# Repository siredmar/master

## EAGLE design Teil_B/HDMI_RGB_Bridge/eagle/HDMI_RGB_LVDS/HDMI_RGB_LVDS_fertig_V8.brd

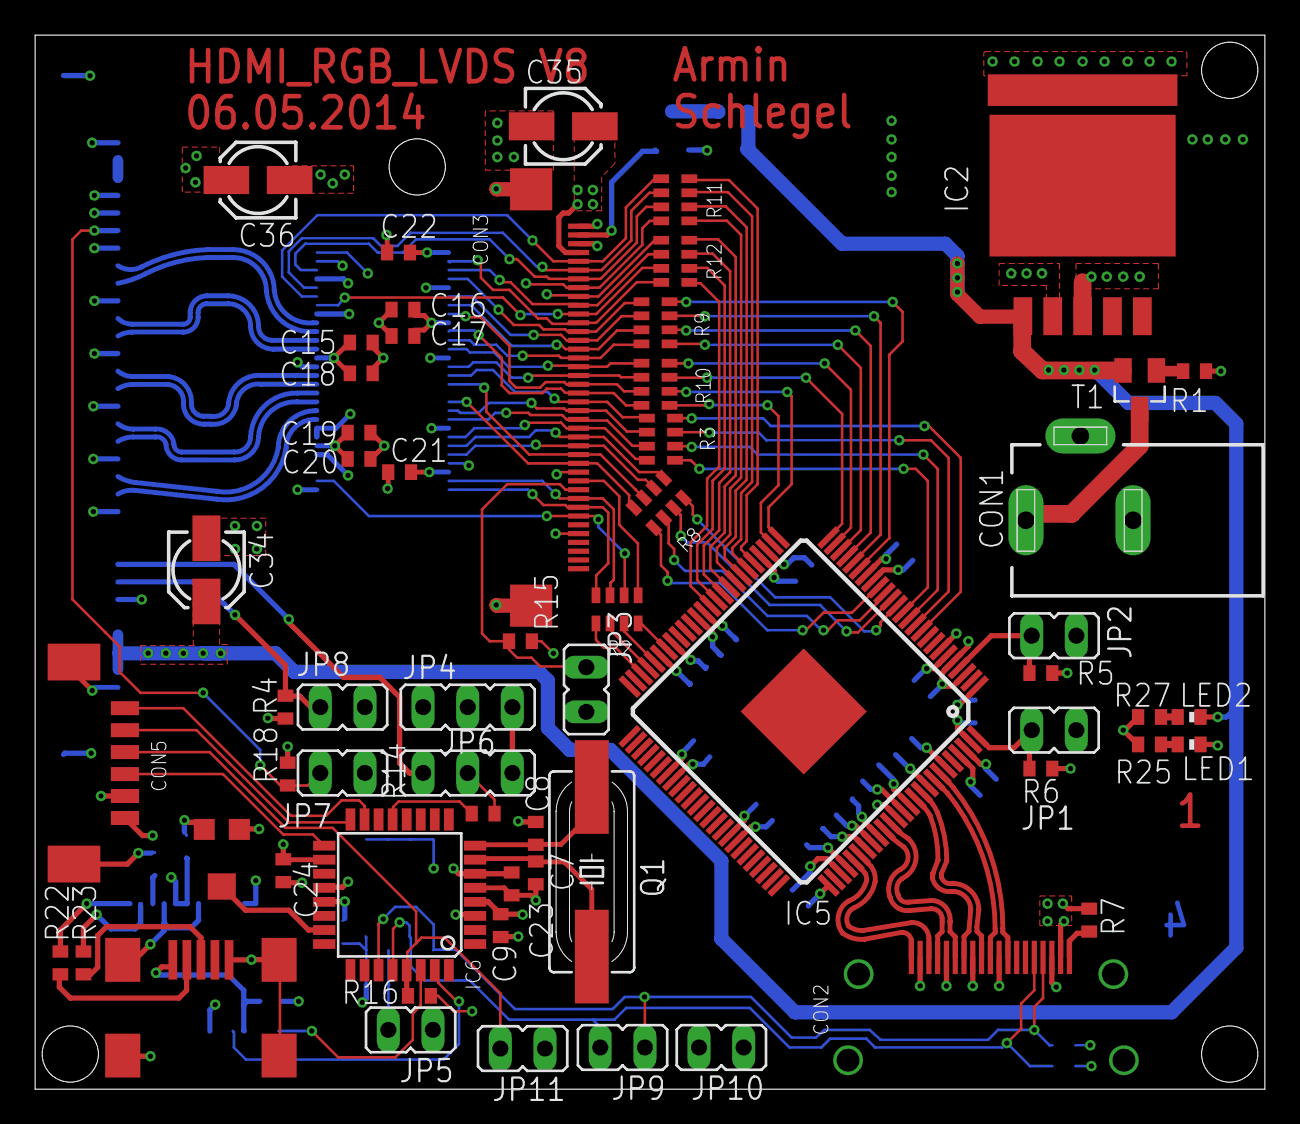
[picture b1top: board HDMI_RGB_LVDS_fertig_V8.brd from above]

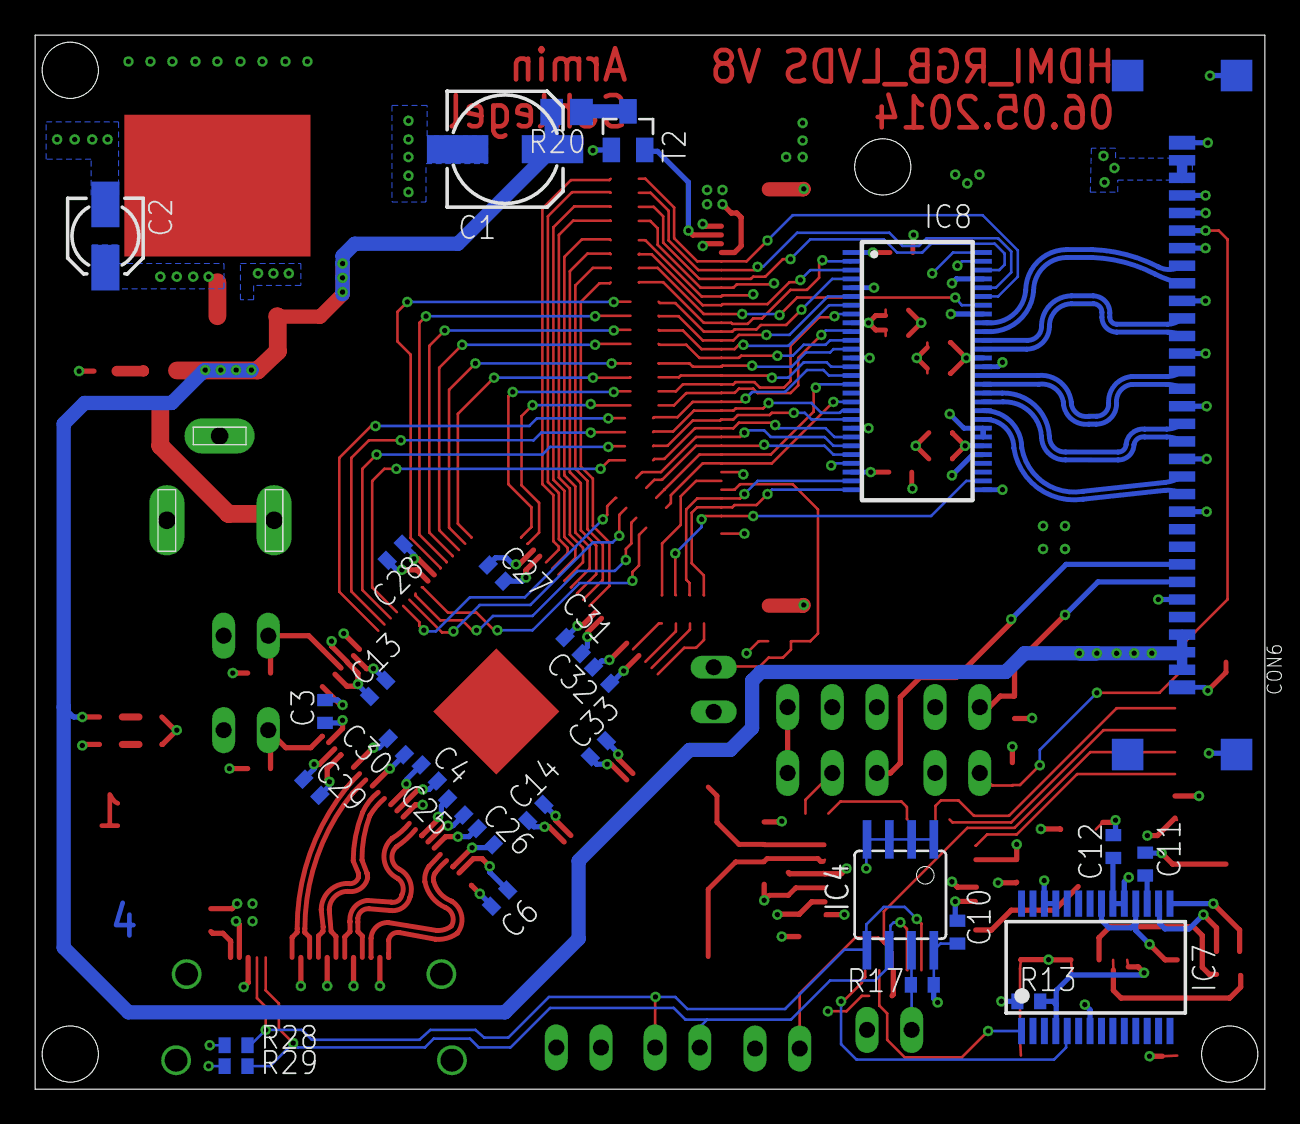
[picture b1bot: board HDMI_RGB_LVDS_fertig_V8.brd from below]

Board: 4 copper layers, 70.0 x 60.0 mm, 95 parts (29 on the bottom side), 113 nets.

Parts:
C1: 100u; C_POL_6X6MM
C2, C34, C35, C36: 10u; C_POL_4X4MM
C3, C4, C6, C9, C10, C11, C12, C13, C14, C16, C18, C20, C23, C24, C25, C26, C27, C28, C29, C30, C31, C32, C33: 100n; C0402
C7, C8: 22p; C0402
C15, C17, C19, C21, C22: 0.01u; C0402
CON1: KLDX-0202-A-LT
CON2: FCI-10029449-111RLF
CON3: XF2M-4015-1A
CON4: FCI-10033526-N3212LF
CON5: MOLEX-53261-0671
CON6: FI-X30SSLA-HF
IC2: WPMDL1300331BD; TO263-5
IC4: AT24C01C-SSHM-B; SOIC8
IC5: TFP401APZP; HTQFP-100
IC6: ATMEGA88PA; TQFP32
IC7: FT232RL; SSOP28
IC8: SN75LVDS83BDGGR; TSSOP-56
JP1, JP2, JP3, JP9, JP10: JUMPER2; JUMPER2_THROUGHHOLE
JP4, JP6: JUMPER3; JUMPER3_THROUGHHOLE
JP5, JP7, JP8, JP11: JUMPER2_THROUGHHOLE
LED1, LED2: LED0402
Q1: ATS073ASM-1; HC49/USSM
R1: 100k; R0402
R2, R3, R8, R9, R10, R11, R12: 22R; R-ARRAY-4X0603
R4, R5, R6, R7, R13, R15, R16, R17, R18: 10k; R0402
R14: 22R; R0402
R19: 5k; 35WR5KLFTR
R20: 15R; R2512
R22, R23: 0R; R0402
R25: 600R; R0402
R27: 2k5; R0402
R28, R29: 4k7; R0402
T1: IRLML5203TRPBF; SOT23
T2: IRLML2502TRPBF; SOT23
U$1, U$2, U$3, U$4, U$5, U$15: FRAME_A3_LANDSCAPE; FRAME

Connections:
+3V3: C2.+, C3.2, C4.2, C6.2, C13.2, C14.2, C15.2, C16.2, C17.2, C18.2, C19.2, C20.2, C21.2, C22.2, C25.2, C26.2, C27.2, C28.2, C29.2, C30.2, C31.2, C32.2, C33.2, C35.+, C36.+, CON3.4, CON6.29, CON6.30, IC2.3, IC5.6, IC5.18, IC5.29, IC5.38, IC5.43, IC5.57, IC5.67, IC5.78, IC5.82, IC5.84, IC5.88, IC5.95, IC5.97, IC5.99, IC8.1, IC8.9, IC8.26, IC8.34, IC8.44, JP4.1, LED1.C, R4.2, R5.2, R6.2, R15.2, R18.2
+5V: C9.1, C10.2, C23.1, C24.1, CON2.18, CON5.5, IC4.8, IC6.4, IC6.6, IC6.18, IC6.20, JP10.2, R7.2, R13.1, R16.1, R17.2, R19.1, R28.2, R29.2
+5V_USB: C12.1, CON4.1, IC7.4, IC7.19, IC7.20, R13.2
+12V: C1.+, C34.+, CON6.1, CON6.2, CON6.3, IC2.1, LED2.C, R20.2, T1.2
AVR_!RESET: CON5.3, IC6.29, JP11.2, R16.2
AVR_MISO: CON5.2, IC6.16
AVR_MOSI: CON5.1, IC6.15
AVR_PWM: JP6.2, R14.2
AVR_PWM_ADC: IC6.23, R19.2
AVR_SCK: CON5.4, IC6.17
AVR_XTAL1: C7.2, IC6.7, Q1.2
AVR_XTAL2: C8.2, IC6.8, Q1.1
EDID_SCL: CON2.15, IC4.6, IC6.28, JP9.2, R29.1
EDID_SDA: CON2.16, IC4.5, IC6.27, JP9.1, R28.1
EDID_WP: IC4.7, JP5.2, R17.1
FTDI_3V3OUT: C11.1, IC7.17
FTDI_RXD: IC6.31, IC7.5
FTDI_TXD: IC6.30, IC7.1
GND: C1.-, C2.-, C3.1, C4.1, C6.1, C7.1, C8.1, C9.2, C10.1, C11.2, C12.2, C13.1, C14.1, C15.1, C16.1, C17.1, C18.1, C19.1, C20.1, C21.1, C22.1, C23.2, C24.2, C25.1, C26.1, C27.1, C28.1, C29.1, C30.1, C31.1, C32.1, C33.1, C34.-, C35.-, C36.-, CON1.2, CON1.3, CON2.2, CON2.5, CON2.8, CON2.11, CON2.17, CON2.GND@1, CON2.GND@2, CON2.GND@3, CON2.GND@4, CON3.1, CON3.3, CON3.29, CON3.36, CON3.GND@1, CON3.GND@2, CON4.5, CON4.GND@1, CON4.GND@2, CON4.GND@3, CON4.GND@4, CON5.6, CON5.GND@1, CON5.GND@2, CON6.5, CON6.10, CON6.13, CON6.16, CON6.19, CON6.22, CON6.25, CON6.27, CON6.28, CON6.GND@1, CON6.GND@2, CON6.GND@3, CON6.GND@4, IC2.2, IC2.6, IC4.1, IC4.2, IC4.3, IC4.4, IC5.1, IC5.3, IC5.5, IC5.7, IC5.19, IC5.28, IC5.39, IC5.45, IC5.58, IC5.68, IC5.76, IC5.79, IC5.83, IC5.87, IC5.89, IC5.92, IC5.98, IC6.3, IC6.5, IC6.21, IC7.7, IC7.18, IC7.21, IC7.25, IC7.26, IC8.5, IC8.13, IC8.21, IC8.25, IC8.29, IC8.33, IC8.35, IC8.36, IC8.43, IC8.49, IC8.53, JP1.1, JP2.1, JP3.1, JP5.1, JP7.1, JP8.1, JP10.1, JP11.1, R1.1, R19.3, R25.1, R27.1
HDMI_CLK_N: CON2.12, IC5.94
HDMI_CLK_P: CON2.10, IC5.93
HDMI_DAT0_N: CON2.9, IC5.91
HDMI_DAT0_P: CON2.7, IC5.90
HDMI_DAT1_N: CON2.6, IC5.86
HDMI_DAT1_P: CON2.4, IC5.85
HDMI_DAT2_N: CON2.3, IC5.81
HDMI_DAT2_P: CON2.1, IC5.80
HDMI_OCK_INV: IC5.100, JP1.2, R6.1
HDMI_PIXS: IC5.4, JP2.2, R5.1
INT_RGB_DE: IC5.46, R2.3M
INT_RGB_EVEN_B0: IC5.10, R3.4M
INT_RGB_EVEN_B1: IC5.11, R3.3M
INT_RGB_EVEN_B2: IC5.12, R3.2M
INT_RGB_EVEN_B3: IC5.13, R3.1M
INT_RGB_EVEN_B4: IC5.14, R8.4M
INT_RGB_EVEN_B5: IC5.15, R8.3M
INT_RGB_EVEN_B6: IC5.16, R8.2M
INT_RGB_EVEN_B7: IC5.17, R8.1M
INT_RGB_EVEN_G0: IC5.20, R9.4M
INT_RGB_EVEN_G1: IC5.21, R9.3M
INT_RGB_EVEN_G2: IC5.22, R9.2M
INT_RGB_EVEN_G3: IC5.23, R9.1M
INT_RGB_EVEN_G4: IC5.24, R10.4M
INT_RGB_EVEN_G5: IC5.25, R10.3M
INT_RGB_EVEN_G6: IC5.26, R10.2M
INT_RGB_EVEN_G7: IC5.27, R10.1M
INT_RGB_EVEN_R0: IC5.30, R11.4M
INT_RGB_EVEN_R1: IC5.31, R11.3M
INT_RGB_EVEN_R2: IC5.32, R11.2M
INT_RGB_EVEN_R3: IC5.33, R11.1M
INT_RGB_EVEN_R4: IC5.34, R12.4M
INT_RGB_EVEN_R5: IC5.35, R12.3M
INT_RGB_EVEN_R6: IC5.36, R12.2M
INT_RGB_EVEN_R7: IC5.37, R12.1M
INT_RGB_HSYNC: IC5.47, R2.2M
INT_RGB_ODCK: IC5.44, R2.4M
INT_RGB_VSYNC: IC5.48, R2.1M
LVDS_0_N: CON6.24, IC8.48
LVDS_0_P: CON6.23, IC8.47
LVDS_1_N: CON6.21, IC8.46
LVDS_1_P: CON6.20, IC8.45
LVDS_2_N: CON6.18, IC8.42
LVDS_2_P: CON6.17, IC8.41
LVDS_3_N: CON6.12, IC8.38
LVDS_3_P: CON6.11, IC8.37
LVDS_CLK_N: CON6.15, IC8.40
LVDS_CLK_P: CON6.14, IC8.39
LVDS_LED_EN: CON6.6, JP8.2, R4.1
LVDS_PWM: CON6.7, JP6.3
LVDS_REVSCAN: CON6.26, JP7.2, R18.1
unnamed: IC6.13, R14.1
unnamed: CON1.1, T1.3
unnamed: R1.2, T1.1
unnamed: IC7.15, R22.2
unnamed: LED1.A, R25.2
unnamed: LED2.A, R27.2
unnamed: IC7.16, R23.2
unnamed: CON2.19, R7.1
unnamed: CON3.2, T2.2
unnamed: R20.1, T2.3
RGB_DE: CON3.34, IC8.30, R2.3P
RGB_DISP: CON3.31, JP3.2, R15.1
RGB_EVEN_B0: CON3.21, IC8.15, R3.4P
RGB_EVEN_B1: CON3.22, IC8.19, R3.3P
RGB_EVEN_B2: CON3.23, IC8.20, R3.2P
RGB_EVEN_B3: CON3.24, IC8.22, R3.1P
RGB_EVEN_B4: CON3.25, IC8.23, R8.4P
RGB_EVEN_B5: CON3.26, IC8.24, R8.3P
RGB_EVEN_B6: CON3.27, IC8.16, R8.2P
RGB_EVEN_B7: CON3.28, IC8.18, R8.1P
RGB_EVEN_G0: CON3.13, IC8.4, R9.4P
RGB_EVEN_G1: CON3.14, IC8.6, R9.3P
RGB_EVEN_G2: CON3.15, IC8.7, R9.2P
RGB_EVEN_G3: CON3.16, IC8.11, R9.1P
RGB_EVEN_G4: CON3.17, IC8.12, R10.4P
RGB_EVEN_G5: CON3.18, IC8.14, R10.3P
RGB_EVEN_G6: CON3.19, IC8.8, R10.2P
RGB_EVEN_G7: CON3.20, IC8.10, R10.1P
RGB_EVEN_R0: CON3.5, IC8.51, R11.4P
RGB_EVEN_R1: CON3.6, IC8.52, R11.3P
RGB_EVEN_R2: CON3.7, IC8.54, R11.2P
RGB_EVEN_R3: CON3.8, IC8.55, R11.1P
RGB_EVEN_R4: CON3.9, IC8.56, R12.4P
RGB_EVEN_R5: CON3.10, IC8.3, R12.3P
RGB_EVEN_R6: CON3.11, IC8.50, R12.2P
RGB_EVEN_R7: CON3.12, IC8.2, R12.1P
RGB_HSYNC: CON3.32, IC8.27, R2.2P
RGB_ODCK: CON3.30, R2.4P
RGB_PWM: JP4.3, JP6.1
RGB_PWM_EN: JP4.2, T2.1
RGB_VSYNC: CON3.33, IC8.28, R2.1P
USB_D+: CON4.3, R23.1
USB_D-: CON4.2, R22.1
